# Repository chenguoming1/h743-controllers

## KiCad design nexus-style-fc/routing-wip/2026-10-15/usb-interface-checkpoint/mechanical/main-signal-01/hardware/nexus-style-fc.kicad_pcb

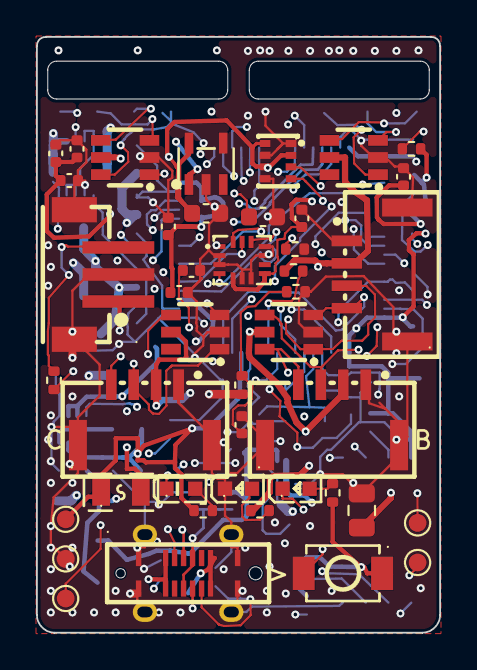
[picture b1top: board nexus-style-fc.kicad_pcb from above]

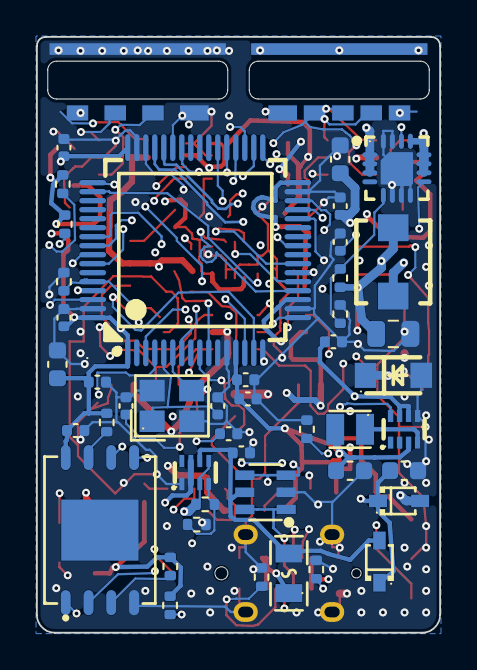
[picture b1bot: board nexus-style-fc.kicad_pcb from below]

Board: 6 copper layers, 22.4 x 33.1 mm, 88 parts (44 on the bottom side), 62 nets.

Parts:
C1, C2, C3, C4, C7, C8, C10, C13, C16, C17, C20, C22, C29, C30: 100nF; C_0402_1005Metric
C5, C9, C27: 4.7uF; C_0603_1608Metric
C6, C18, C25: 1uF; C_0402_1005Metric
C11, C12: 30pF; C_0402_1005Metric
C14: 2.2uF; C_0402_1005Metric
C15: 10nF; C_0402_1005Metric
C19, C21: 10uF; C_0603_1608Metric
C23: 3.3nF; C_0402_1005Metric
C24, C26: 22uF; C_0805_2012Metric
C28: 22uF; C_0603_1608Metric
D1: LED1 yellow-green; LED0603-RD_GREEN
D2: LED2 red; LED0603-RD_RED
D3: Power LED blue; LED0603-RD_BLUE
D4: SMF13A; SOD-123FL_L2.8-W1.8-LS3.6-RD
D5, D6: B5819WS; SOD-323_L1.8-W1.3-LS2.5-RD
F1, F2: 0.5A PTC; F0805
J1: Header child board; HeaderBoard_Joint
J2: DSM (UART1); CONN-SMD_B3B-ZR-SM4-TF
J3: A-CRSF (UART4); CONN-SMD_4P-P1.25_BM04B-GHS-TBT-LF-SN
J4: C (UART3); CONN-SMD_4P-P1.25_BM04B-GHS-TBT-LF-SN
J5: B (UART6); CONN-SMD_4P-P1.25_BM04B-GHS-TBT-LF-SN
J6: USB-C vertical; USB-C-SMD_TYPE-C-31-D-06
L1: 2.2uH 3A; IND-SMD_L4.6-W4.1
L2: 2.2uH; IND-SMD_L2.0-W1.6
R1, R5, R8, R9, R10, R17, R19: 10k; R_0402_1005Metric
R2, R3, R4, R22: 1k; R_0402_1005Metric
R6, R7: 2.2k; R_0402_1005Metric
R11: 120k; R_0402_1005Metric
R12: 22k; R_0402_1005Metric
R13: 100k; R_0402_1005Metric
R14: 27k; R_0402_1005Metric
R15: 27.4k; R_0402_1005Metric
R16: 52.3k; R_0402_1005Metric
R18: 21k; R_0402_1005Metric
R20, R21: 5.1k; R_0402_1005Metric
SW1: BOOT; SW-SMD_L3.9-W3.0-P4.45
TP1: SWDIO; TestPoint_Pad_D1.0mm
TP2: SWCLK; TestPoint_Pad_D1.0mm
TP3: 3V3; TestPoint_Pad_D1.0mm
TP4: GND; TestPoint_Pad_D1.0mm
TP5: NRST; TestPoint_Pad_D1.0mm
U1: STM32F722RET6; LQFP-64_L10.0-W10.0-P0.50-LS12.0-BL
U2: ICM-42688-P; LGA-14_L3.0-W2.5-P0.50-TL
U3: DPS368XTSA1; LGA-8_L2.5-W2.0-P0.65-TR_DPS368
U4: W25N01GVZEIG; WSON-8_L8.0-W6.10-P1.27-BL-EP
U5: TPS62130RGTR; QFN-16_L3.0-W3.0-P0.50-TL-EP1.7
U7: USBLC6-2SC6; SOT-23-6_L2.9-W1.6-P0.95-LS2.8-BL
U9: TPS2116DRLR; SOT-583-8_L2.1-W1.6-P0.50-LS1.6-BL
U10: TPS70933DBVR; SOT-23-5_L3.0-W1.7-P0.95-LS2.8-BL
U11, U12, U13, U15: SRV05-4; SOT-23-6_L2.9-W1.6-P0.95-LS2.8-BR
U14: TPS629210DRLR; SOT-5X3-8_L2.1-W1.2-P0.50-LS1.6-BL_DRL0008A
Y1: 8MHz 20pF; CRYSTAL-SMD_4P-L3.2-W2.5-BL

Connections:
3V3: C1.1, C2.1, C3.1, C4.1, C5.1, C6.1, C7.1, C8.1, C20.1, C28.1, F2.1, L2.2, R2.1, R3.1, R8.2, R9.2, R10.2, SW1.2, TP3.1, U1.1, U1.13, U1.19, U1.32, U1.48, U1.64, U4.8, U14.3
3V3_DSM: F2.2, J2.1
3V3_SENS: C13.1, C14.1, C15.1, C16.1, C17.1, C19.1, R5.2, R6.2, R7.2, U2.5, U2.8, U3.2, U3.6, U3.8, U10.5
5V: C26.1, J3.2, J4.2, J5.2, R4.1, R18.1, U9.2, U9.7, U11.5, U12.5, U13.5, U15.5
5V_BUCK: C24.1, L1.2, R11.1, R13.1, U5.14, U9.3, U9.5
5V_SENSE: C30.1, R18.2, R19.1, U1.10
A_RX: J3.3, U1.14, U13.1
A_TX: J3.4, U1.15, U13.3
BOOT0: R1.1, SW1.1, U1.60
B_RX: J5.3, U1.37, U13.4
B_TX: J5.4, U1.38, U13.6
CC1: J6.A5, R20.1
CC2: J6.B5, R21.1
C_RX: J4.3, U1.28, U15.1
C_TX: J4.4, U1.29, U15.3
DSM_DATA: J2.3, R22.2, U1.43, U15.4
DSM_TX: R22.1, U1.42
ESC: J1.5, U1.58, U11.4
FB_5V: R11.2, R12.1, U5.5
FLASH_CS: R8.1, U1.33, U4.1
FLASH_HOLD: R10.1, U4.7
FLASH_WP: R9.1, U4.3
GND: C1.2, C2.2, C3.2, C4.2, C5.2, C6.2, C7.2, C8.2, C9.2, C10.2, C11.2, C12.2, C13.2, C14.2, C15.2, C16.2, C17.2, C18.2, C19.2, C20.2, C21.2, C22.2, C23.2, C24.2, C25.2, C26.2, C27.2, C28.2, C29.2, C30.2, D3.1, D4.2, J1.2, J2.2, J2.4, J2.5, J3.1, J3.5, J3.6, J4.1, J4.5, J4.6, J5.1, J5.5, J5.6, J6.A1, J6.A12, J6.B1, J6.B12, J6.EP, R1.2, R12.2, R14.2, R15.2, R17.2, R19.2, R20.2, R21.2, TP4.1, U1.12, U1.18, U1.31, U1.47, U1.63, U2.2, U2.3, U2.6, U2.7, U2.10, U2.11, U3.1, U3.5, U3.7, U4.4, U5.6, U5.7, U5.8, U5.15, U5.16, U5.17, U7.2, U9.1, U10.2, U11.2, U12.2, U13.2, U14.5, U15.2, Y1.2, Y1.4
I2C1_SCL: R6.1, U1.61, U3.4
I2C1_SDA: R7.1, U1.62, U3.3
IMU_CS: R5.1, U1.20, U2.12
IMU_INT: U1.50, U2.4
LED1_A: D1.2, R2.2
LED1_K: D1.1, U1.3
LED2_A: D2.2, R3.2
LED2_K: D2.1, U1.4
LED3_A: D3.2, R4.2
NRST: C10.1, TP5.1, U1.7
OSC_IN: C11.1, U1.5, Y1.1
OSC_OUT: C12.1, U1.6, Y1.3
PR1: R13.2, R14.1, U9.4
RPM: J1.4, U1.16, U11.3
S1: J1.9, U1.56, U12.4
S2: J1.8, U1.57, U12.3
S3: J1.7, U1.25, U12.1
SBUS: J1.3, U1.17, U11.1
SCONF: R15.1, U14.8
SPI1_MISO: U1.22, U2.1
SPI1_MOSI: U1.23, U2.14
SPI1_SCK: U1.21, U2.13
SPI2_MISO: U1.35, U4.2
SPI2_MOSI: U1.36, U4.5
SPI2_SCK: U1.34, U4.6
SS_5V: C23.1, U5.9
SWCLK: TP2.1, U1.49
SWDIO: TP1.1, U1.46
SW_3V3: L2.1, U14.4
SW_5V: L1.1, U5.1, U5.2, U5.3
TAIL: J1.6, U1.55, U11.6
USB_DM: J6.A7, J6.B7, U1.44, U7.1, U7.6
USB_DP: J6.A6, J6.B6, U1.45, U7.3, U7.4
VBUS: C25.1, D6.2, F1.2, U7.5, U9.6
VBUS_C: F1.1, J6.A4, J6.A9, J6.B4, J6.B9
VCAP: C9.1, U1.30
VSYS: C18.1, C27.1, D5.1, D6.1, U10.1, U14.6, U14.7
VX: C21.1, C22.1, D4.1, D5.2, J1.1, R16.1, U5.10, U5.11, U5.12, U5.13
VX_SENSE: C29.1, R16.2, R17.1, U1.9

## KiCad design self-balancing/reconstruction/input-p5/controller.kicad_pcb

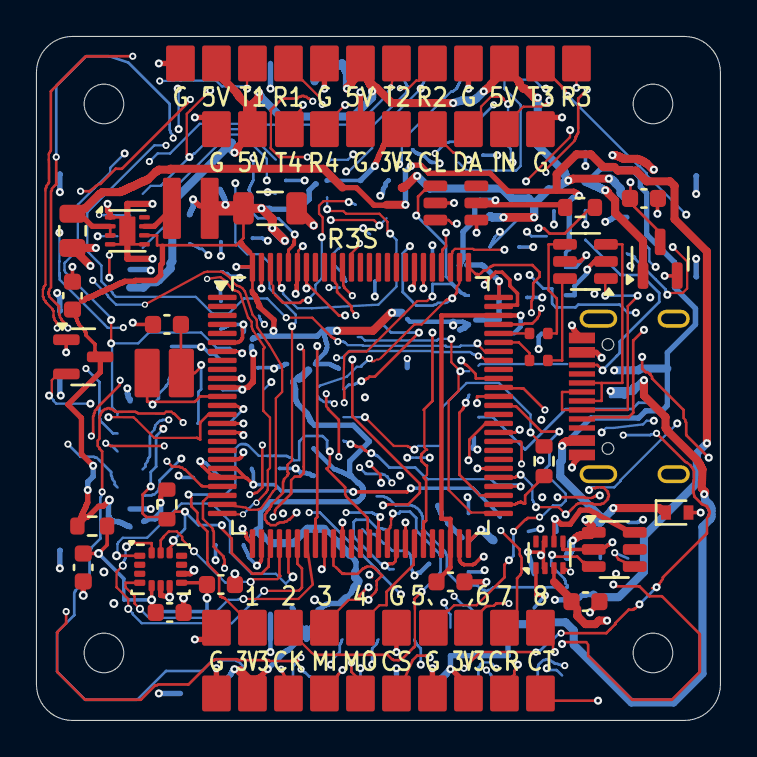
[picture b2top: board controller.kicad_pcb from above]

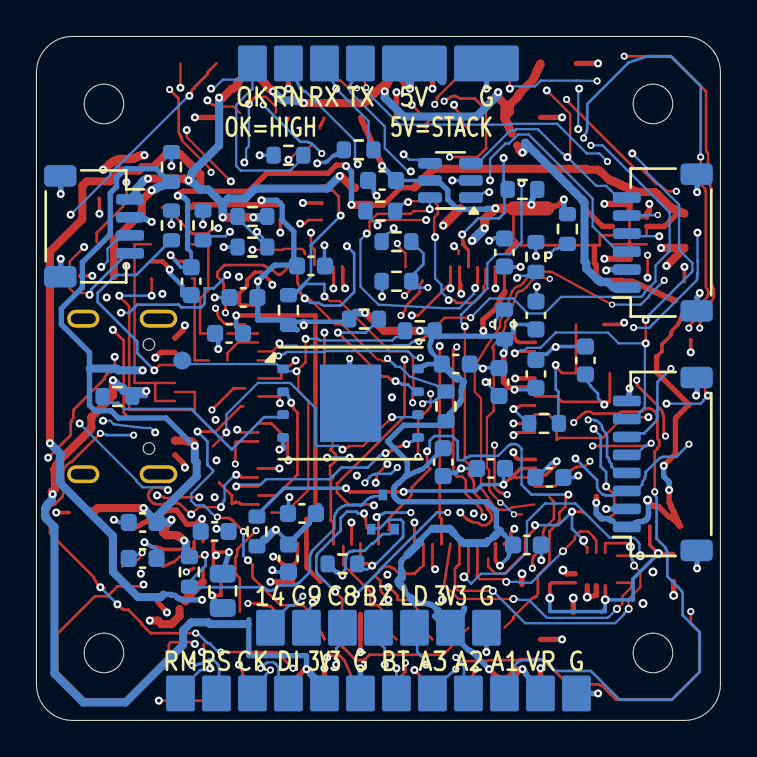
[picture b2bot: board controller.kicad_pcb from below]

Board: 6 copper layers, 38.0 x 38.0 mm, 151 parts (76 on the bottom side), 85 nets.

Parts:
C1, C41: 10uF / 25V; C_0805_2012Metric
C2: 22uF / 25V; C_1206_3216Metric
C3, C6, C7, C8, C9, C11, C12, C15, C16, C24, C25, C29, C31, C32, C38: 100nF / 50V; C_0603_1608Metric
C4, C10, C33: 1uF / 50V; C_0603_1608Metric
C5, C14: 10nF / 50V; C_0603_1608Metric
C13, C39, C40: 2.2uF / 16V; C_0603_1608Metric
C26: 10uF / 10V; C_0603_1608Metric
C34, C35: 18pF C0G / tune; C_0603_1608Metric
C36, C37: 2.2uF / VCAP; C_0603_1608Metric
D4: ESDA7P120-1U1M; ST_QFN-2L_1.6x1.0mm_DS14419
H1, H2, H3, H4: MountingHole_2.2mm_M2
J2: TYPE-C-31-M-12; USB_C_HRO_TYPE-C-31-M-12_EdgeSilk
J3: MOTOR / 6-wire; LianXin_XDWF-0910_06P_Horizontal
J4: EXT SPI SENSOR; JST_SH_SM08B-SRSS-TB_1x08-1MP_P1.00mm_Horizontal
J5: GPS / UART4; JST_SH_SM04B-SRSS-TB_1x04-1MP_P1.00mm_Horizontal
J101, J105, J109, J113, J117, J122, J123, J129, J133, J138, J149, J155, J161: G; WirePad_1.6x2.0mm
J102, J106, J110, J114: 5V; WirePad_1.6x2.0mm
J103: T1; WirePad_1.6x2.0mm
J104: R1; WirePad_1.6x2.0mm
J107: T2; WirePad_1.6x2.0mm
J108: R2; WirePad_1.6x2.0mm
J111: T3; WirePad_1.6x2.0mm
J112: R3; WirePad_1.6x2.0mm
J115: T4; WirePad_1.6x2.0mm
J116: R4; WirePad_1.6x2.0mm
J118, J124, J130, J156, J162: 3V3; WirePad_1.6x2.0mm
J119: SCL; WirePad_1.6x2.0mm
J120: SDA; WirePad_1.6x2.0mm
J121: INT; WirePad_1.6x2.0mm
J125: SCK; WirePad_1.6x2.0mm
J126: MISO; WirePad_1.6x2.0mm
J127: MOSI; WirePad_1.6x2.0mm
J128: CS; WirePad_1.6x2.0mm
J131: CAN_RX; WirePad_1.6x2.0mm
J132: CAN_TX; WirePad_1.6x2.0mm
J134: OUT1; WirePad_1.6x2.0mm
J135: OUT2; WirePad_1.6x2.0mm
J136: OUT3; WirePad_1.6x2.0mm
J137: OUT4; WirePad_1.6x2.0mm
J139: OUT5; WirePad_1.6x2.0mm
J140: OUT6; WirePad_1.6x2.0mm
J141: OUT7; WirePad_1.6x2.0mm
J142: OUT8; WirePad_1.6x2.0mm
J143: G_LINK; WirePad_3.6x2.0mm
J144: 5V_LINK; WirePad_3.6x2.0mm
J145: LINK_TX; WirePad_1.6x2.0mm
J146: LINK_RX; WirePad_1.6x2.0mm
J147: RUN; WirePad_1.6x2.0mm
J148: M_OK; WirePad_1.6x2.0mm
J150: VTREF; WirePad_1.6x2.0mm
J151: SWDIO; WirePad_1.6x2.0mm
J152: SWCLK; WirePad_1.6x2.0mm
J153: NRST; WirePad_1.6x2.0mm
J154: BOOT; WirePad_1.6x2.0mm
J157: ADC1; WirePad_1.6x2.0mm
J158: ADC2; WirePad_1.6x2.0mm
J159: ADC3; WirePad_1.6x2.0mm
J160: RPM; WirePad_1.6x2.0mm
J163: LED; WirePad_1.6x2.0mm
J164: BUZ; WirePad_1.6x2.0mm
J165: PC8; WirePad_1.6x2.0mm
J166: PC9; WirePad_1.6x2.0mm
J167: PD14; WirePad_1.6x2.0mm
L1: 3.3uH / VLS3012HBX; TDK_VLS3012HBX
Q1: 2N7002; SOT-23
Q2: DMN2310UW-7; DMN2310UW_SOT323
R1, R2: 10R; R_0603_1608Metric
R3, R4, R11, R12, R13, R43, R46, R48, R49, R50, R53, R54, R55, R56: 10k; R_0603_1608Metric
R5, R6: 5.1k; R_0603_1608Metric
R7, R8: 0R; R_0402_1005Metric_R3S_NoSilk
R9, R10, R45: 4.7k; R_0603_1608Metric
R42, R44: 47k; R_0603_1608Metric
R51, R52, R57: 33R; R_0603_1608Metric
R58: 0R / HSE tune; R_0603_1608Metric
TP1: FLASH_CS service; TestPoint_Pad_D1.0mm_R3S_NoRing
U1: STM32H743VIT6; LQFP-100_14x14mm_P0.5mm
U2: TPS62162DSGR / 3.3V; TPS62162_DSG_R3S
U3: ICM-42688-P; LGA-14_3x2.5mm_P0.5mm_LayoutBorder3x4y
U4: USBLC6-2SC6; SOT-23-6
U6: TPS22918DBVR; SOT-23-6
U8: TPS3700DDCR; TSOT-23-6_R3S_ClearLabels
U10: SN74LVC2G17DBVR; SOT-23-6
U11: W25N01GVZEIG / 128MiB; WSON-8-1EP_8x6mm_P1.27mm_EP3.4x4.3mm
U12: TLV803EA29DBZR; SOT-23
U13: TPS2116DRLR; SOT-583-8
X1: 8MHz / CL12pF; TXC_A308000003_3225_2pad

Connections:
3V3_CORE: C2.1, C3.1, C6.1, C7.1, C8.1, C9.1, C25.1, C26.1, C29.1, C31.1, C32.1, C33.1, C38.1, J4.1, J118.1, J124.1, J130.1, J150.1, J156.1, J162.1, L1.2, R1.1, R2.1, R4.1, R9.1, R10.1, R11.1, R13.1, R46.1, R53.1, R54.1, R55.1, R56.1, U1.6, U1.11, U1.27, U1.50, U1.75, U1.100, U2.6, U8.5, U10.5, U11.8, U12.3
+5V_STACK: C39.1, J3.1, J5.1, J102.1, J106.1, J110.1, J114.1, J144.1, R44.1, U13.3
/clock/HSE_XOUT: C35.1, R58.2, X1.2
/power/BUCK_SW: L1.1, U2.7
/power/STACK_5V_DIV: R44.2, R45.1, U8.3
/power/USB_CC1: J2.A5, R5.1
/power/USB_CC2: J2.B5, R6.1
/power/USB_DM_CONN: J2.A7, J2.B7, U4.1
/power/USB_DM_ESD: R7.1, U4.6
/power/USB_DP_CONN: J2.A6, J2.B6, U4.3
/power/USB_DP_ESD: R8.1, U4.4
/power/USB_SLEW_CT: C5.1, U6.4
/power/USB_SWITCH_ON: Q2.3, R42.2, U6.3
/power/USB_VBUS_SLEW: C40.1, U6.6, U13.6
/storage/FLASH_HOLD_n: R55.2, U11.7
/storage/FLASH_SCLK: R57.2, U11.6
/storage/FLASH_WP_n: R54.2, U11.3
ADC1_RAW: J157.1, U1.15
ADC2_RAW: J158.1, U1.16
ADC3_RAW: J159.1, U1.23
AUX_PC8: J165.1, U1.65
AUX_PC9: J166.1, U1.66
AUX_PD14: J167.1, U1.61
BOOT0: J154.1, R3.1, U1.94
BUZZER_CTRL: J164.1, U1.35
EXT_I2C_SCL: J119.1, R9.2, U1.95
EXT_I2C_SDA: J120.1, R10.2, U1.96
EXT_SENSOR_INT: J4.7, J121.1, U1.7
EXT_SPI_CS: J4.6, J128.1, R56.2, U1.77
EXT_SPI_MISO: J4.5, J126.1, U1.90
EXT_SPI_MOSI: J4.4, J127.1, U1.91
EXT_SPI_SCK: J4.3, J125.1, U1.89
FDCAN1_RX: J131.1, U1.81
FDCAN1_TX: J132.1, U1.82
FLASH_CS: R53.2, TP1.1, U1.51, U11.1
FLASH_MISO: U1.53, U11.2
FLASH_MOSI: U1.54, U11.5
FLASH_SCLK_RAW: R57.1, U1.52
GND: C1.2, C2.2, C3.2, C4.2, C5.2, C6.2, C7.2, C8.2, C9.2, C10.2, C11.2, C12.2, C13.2, C14.2, C15.2, C16.2, C24.2, C25.2, C26.2, C29.2, C31.2, C32.2, C33.2, C34.2, C35.2, C36.2, C37.2, C38.2, C39.2, C40.2, C41.2, D4.2, J2.A1, J2.A12, J2.B1, J2.B12, J2.S1, J3.2, J3.MP, J4.2, J4.8, J4.MP, J5.2, J5.MP, J101.1, J105.1, J109.1, J113.1, J117.1, J122.1, J123.1, J129.1, J133.1, J138.1, J143.1, J149.1, J155.1, J161.1, Q1.2, Q2.2, R3.2, R5.2, R6.2, R12.2, R43.2, R45.2, R48.2, R49.2, R50.2, U1.10, U1.19, U1.26, U1.49, U1.74, U1.99, U2.1, U2.4, U2.5, U2.9, U3.6, U3.7, U3.9, U4.2, U6.2, U8.2, U8.4, U10.2, U11.4, U11.9, U12.1, U13.1, U13.4, U13.5
HOST_RUN_LINK: J3.5, J147.1, R52.2
HOST_RUN_RAW: R50.1, R52.1, U1.33
HOST_TX_LINK: J3.3, J145.1, R51.2
HOST_TX_RAW: R51.1, U1.98
HSE_IN: C34.1, U1.12, X1.1
HSE_OUT: R58.1, U1.13
IMU_3V3: C12.1, C13.1, C14.1, R2.2, U3.5, U3.8
IMU_CS: R13.2, U1.28, U3.12
IMU_INT: U1.32, U3.4
IMU_MISO: U1.30, U3.1
IMU_MOSI: U1.31, U3.14
IMU_SCLK: U1.29, U3.13
LED_DATA: J163.1, U1.34
MOTOR_OK_BUF: U1.36, U10.4
MOTOR_OK_LINK: J3.6, J148.1, R49.1, U10.3
MOTOR_TX_BUF: U1.97, U10.6
MOTOR_TX_LINK: J3.4, J146.1, R48.1, U10.1
NRST: C15.1, J153.1, R4.2, U1.14, U12.2
OUT1: J134.1, U1.39
OUT2: J135.1, U1.41
OUT3: J136.1, U1.43
OUT4: J137.1, U1.44
OUT5: J139.1, U1.63
OUT6: J140.1, U1.64
OUT7: J141.1, U1.59
OUT8: J142.1, U1.60
RPM_IN: J160.1, U1.22
STACK_5V_GOOD: R46.2, U1.45, U8.1
SWCLK: J152.1, U1.76
SWDIO: J151.1, U1.72
UART1_RX: J104.1, U1.69
UART1_TX: J103.1, U1.68
UART2_RX: J108.1, U1.25
UART2_TX: J107.1, U1.24
UART3_RX: J112.1, U1.56
UART3_TX: J111.1, U1.55
UART4_RX: J5.4, J116.1, U1.79
UART4_TX: J5.3, J115.1, U1.78
USB_DM_MCU: R7.2, U1.70
USB_DP_MCU: R8.2, U1.71
USB_PRESENT_n: C16.1, Q1.3, R11.2, U1.40
USB_SOURCE_DISABLE: Q2.1, R43.1, U1.42
USB_VBUS: C4.1, D4.1, J2.A4, J2.A9, J2.B4, J2.B9, Q1.1, R12.1, R42.1, U6.1
VCAP: C36.1, C37.1, U1.48, U1.73
VDDA: C10.1, C11.1, R1.2, U1.20, U1.21
VLOGIC_IN: C1.1, C24.1, C41.1, U2.2, U2.3, U4.5, U13.2, U13.7
